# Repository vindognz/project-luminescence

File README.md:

# ✨ **Project Luminescence** ✨

Project Luminescence is a custom heart shaped PCB with 10 red LEDs and a trimpot for analog brightness control.

Flip the switch on the back, then press the button on the front to cycle between off, on, and a slow fade mode. Use the trimpot on the back to tune the brightness.

I designed this as a birthday present for my girlfriend!

## Hardware:
- ATtiny85 microcontroller!
- Back-mounted CR2032
- 10x 5mm red LEDs around the PCB perimeter
- 6mm tactile button for mode cycling
- 1kΩ potentiometer for manual brightness tuning
- Back mounted SPDT slide switch as a master on/off switch
- 70x70mm, 2 layer blue PCB with white silkscreen and a ground pour

## CAD Model:
I opted for a pretty PCB instead of any form of case, so no 3D design files.

However, I was scared to omit this section, so `cad/pcb.step` is just the populated PCB, exported from KiCad.

## PCB:
This is my PCB. I designed it in KiCad!

## Firmware Features
- 50ms button debouncing
- Press the button to cycle OFF ⇨ ON ⇨ FADE 
- Gamma corrected smooth sine wave breathing
- Analog trimpot brightness control

## BOM
The full bill of materials with links and USD prices is in [`BOM.csv`](BOM.csv)

## Showcase
Check it out in action:

[Watch the showcase video](https://www.youtube.com/watch?v=EI6_KILgyM8)

### Thanks for voting :)

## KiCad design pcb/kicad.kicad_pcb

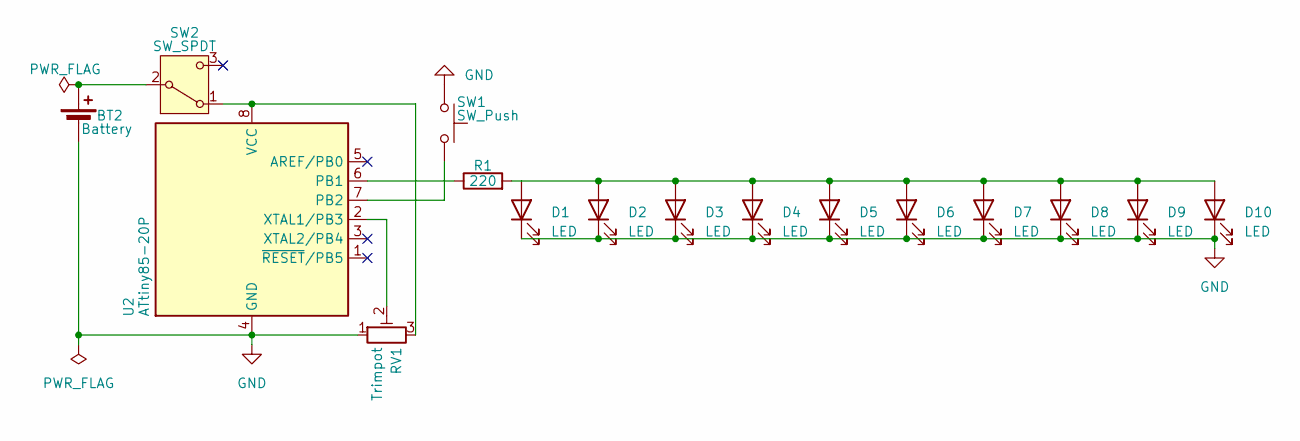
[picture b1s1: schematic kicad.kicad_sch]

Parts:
BT2: Battery; BatteryHolder_MYOUNG_BS-07-A1BJ001_CR2032
D1, D2, D3, D4, D5, D6, D7, D8, D9, D10: LED; LED_D5.0mm
R1: 220; R_Axial_DIN0207_L6.3mm_D2.5mm_P10.16mm_Horizontal
RV1: Trimpot; Potentiometer_Runtron_RM-065_Vertical
SW1: SW_Push; SW_PUSH_6mm
SW2: SW_SPDT; SW_Slide-03_Wuerth-WS-SLTV_10x2.5x6.4_P2.54mm
U2: ATtiny85-20P; DIP-8_W7.62mm

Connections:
GND: BT2.2 (-), D1.1 (K), D2.1 (K), D3.1 (K), D4.1 (K), D5.1 (K), D6.1 (K), D7.1 (K), D8.1 (K), D9.1 (K), D10.1 (K), RV1.1, SW1.1, U2.4 (GND)
unnamed: BT2.1 (+), SW2.2 (B)
unnamed: D1.2 (A), D2.2 (A), D3.2 (A), D4.2 (A), D5.2 (A), D6.2 (A), D7.2 (A), D8.2 (A), D9.2 (A), D10.2 (A), R1.2
unnamed: RV1.3, SW2.1 (A), U2.8 (VCC)
unnamed: R1.1, U2.6 (PB1)
unnamed: SW1.2, U2.7 (PB2)
unnamed: RV1.2, U2.2 (XTAL1/PB3)

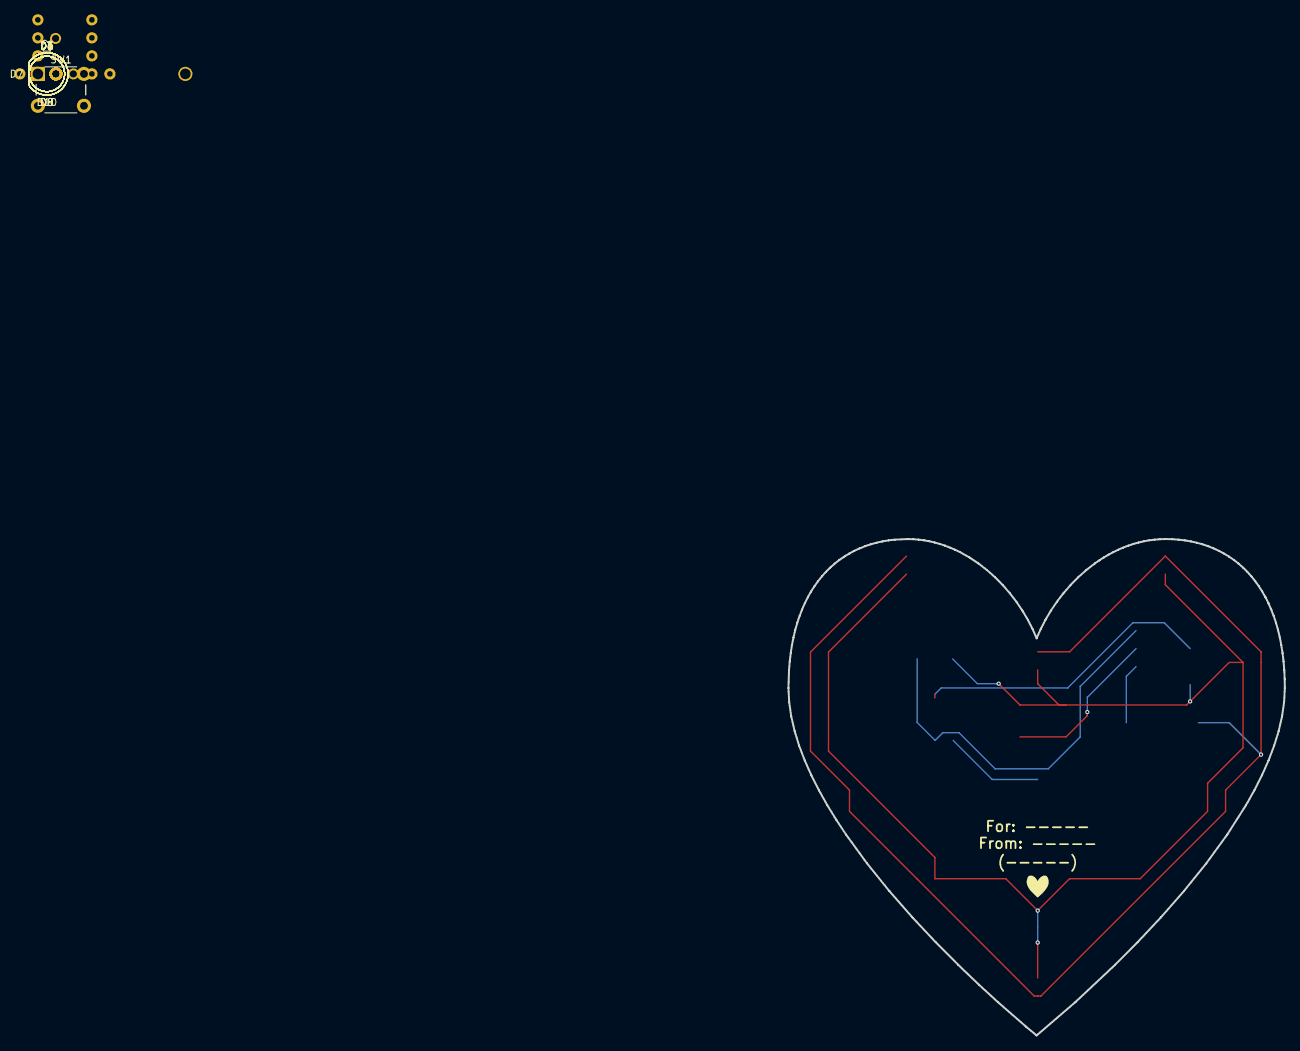
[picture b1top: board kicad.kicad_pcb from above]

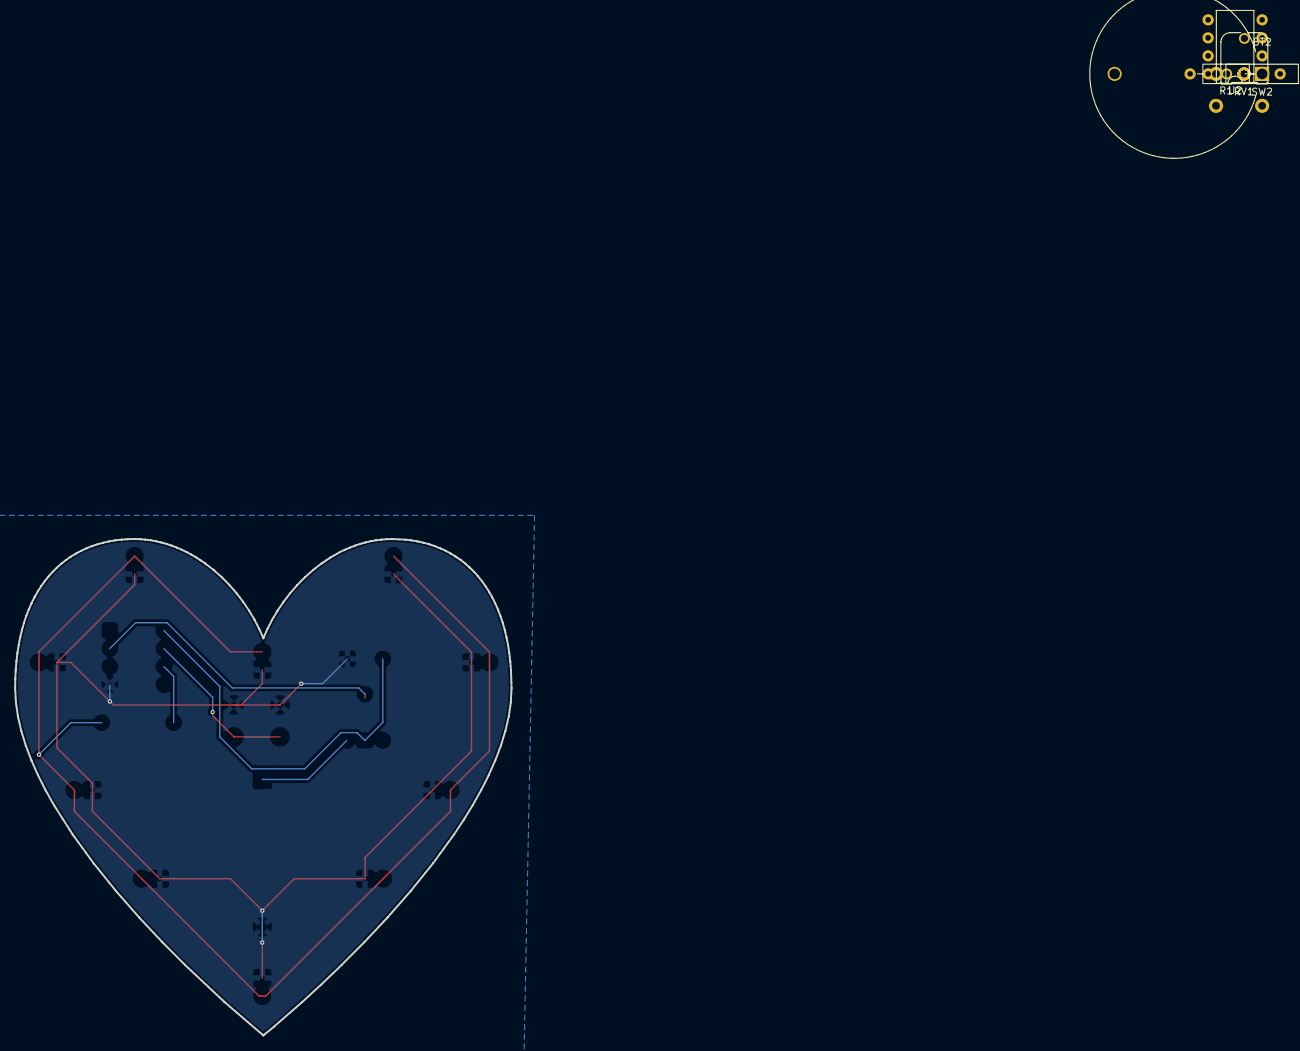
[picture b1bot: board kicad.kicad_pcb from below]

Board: 2 copper layers, 70.0 x 70.0 mm, 16 parts (5 on the bottom side), 7 nets.

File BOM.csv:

Item Name,Qty,Price (total) (USD),Item link,Notes
ATtiny85-20PU,1,$12.38,https://www.aliexpress.com/item/1005007456620827.html,
Red 5mm LEDs,10,$4.03,https://www.aliexpress.com/item/1005009812533874.html,Sourced from a kit. Equivalent part linked.
180Ω Resistor,1,$0.82,https://www.aliexpress.com/item/1005011894987526.html,"Used 180Ω on the board, 220Ω in the design.
Sourced from a kit. Equivalent part linked."
1kΩ Trimpot 3362P,1,$4.56,https://www.aliexpress.com/item/1005010523079544.html,
6mm Tactile Button,1,$3.17,https://www.aliexpress.com/item/1005007093840619.html,Sourced from a kit. Equivalent part linked.
SS12D00 Slide Switch,1,$3.24,https://www.aliexpress.com/item/1005010111050912.html,
CR2032 Battery,1,$0.53,https://www.aliexpress.com/item/1005005712983454.html,"I bought mine from my local supermarket.
Equivalent part linked."
CR2032 Battery Holder,1,$4.44,https://www.aliexpress.com/item/1005007335928261.html,
Blank PCB (JLCPCB),1,$4.80,https://cart.jlcpcb.com/quote,"2 layer, 70x70mm, blue mask, white silkscreen, qty 5"
Shipping,,$3.86,,Shipping for the orders that weren't free
,,,,
Total Price (USD):,$41.83,,,

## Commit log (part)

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2026-06-05 Initial Commit!
2026-06-05 Session #1: README update, designed the whole board lol
2026-06-05 Session #1: Removed kicad/.history
2026-06-05 Session #2: Firmware skeleton
2026-06-05 Session #2: ready for breadboard test
2026-06-05 Session #2: fixing syntax errors
2026-06-06 Session #2: add button debouncing with 50ms delay
2026-06-06 Session #2: mode cycling (off, on, blinking modes working)
2026-06-06 Session #2: readme update and polish
2026-06-15 Session #3: Smooth PWM breathing fade + gamma correction
2026-06-21 Session #4: Trimpot brightness control, README update
